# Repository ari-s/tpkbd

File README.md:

TPKBD - a USB interface for thinkpad keyboards
=

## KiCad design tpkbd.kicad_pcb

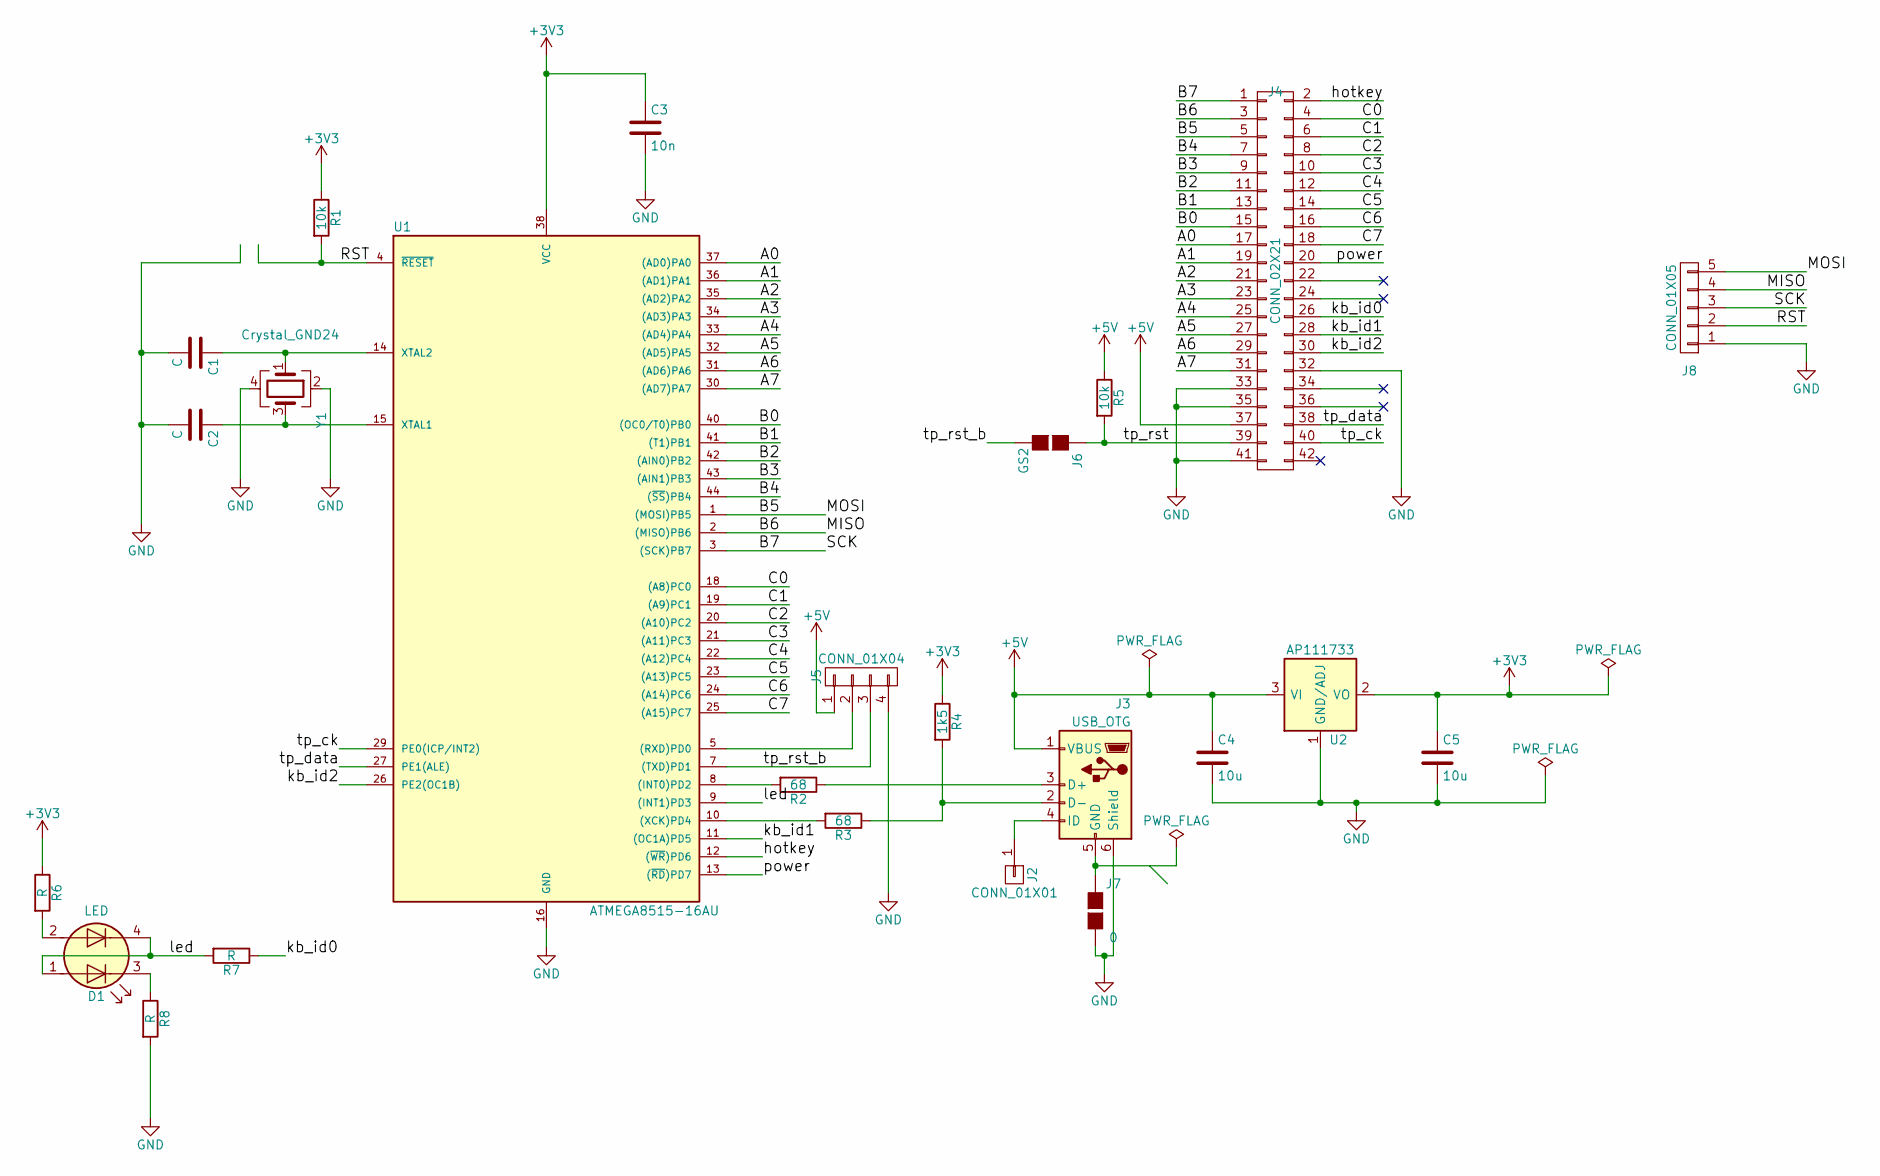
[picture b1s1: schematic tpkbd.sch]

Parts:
C1, C2: C; C_0603_HandSoldering
C3: 10n; C_0603_HandSoldering
C4, C5: 10u; C_0805_HandSoldering
D1: LED; PLCC4
J2: CONN_01X01; Pins1x1
J3: USB_OTG; USB_Micro-B
J4: CONN_02X21; KX14
J5: CONN_01X04; Pin_Header_Straight_1x04
J6: GS2; C_0402
J7: 0; C_0402
J8: CONN_01X05; Pins_1x5
R1, R5: 10k; R_0603_HandSoldering
R2, R3: 68; R_0603_HandSoldering
R4: 1k5; R_0603_HandSoldering
R6, R7, R8: R; R_0603_HandSoldering
U1: ATMEGA8515-16AU; LQFP-44_10x10mm_Pitch0.8mm
U2: AP111733; SOT-223
Y1: Crystal_GND24; Crystal_SMD_0603_4Pads

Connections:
+3V3: C3.1, C5.1, R1.1, R4.1, R6.1, U1.38 (VCC), U2.2 (VO), U2.4 (VO)
+5V: C4.1, J3.1 (VBUS), J4.37, J5.1, R5.1, U2.3 (VI)
/A0: J4.17, U1.37 ((AD0)PA0)
/A1: J4.19, U1.36 ((AD1)PA1)
/A2: J4.21, U1.35 ((AD2)PA2)
/A3: J4.23, U1.34 ((AD3)PA3)
/A4: J4.25, U1.33 ((AD4)PA4)
/A5: J4.27, U1.32 ((AD5)PA5)
/A6: J4.29, U1.31 ((AD6)PA6)
/A7: J4.31, U1.30 ((AD7)PA7)
/B0: J4.15, U1.40 ((OC0/T0)PB0)
/B1: J4.13, U1.41 ((T1)PB1)
/B2: J4.11, U1.42 ((AIN0)PB2)
/B3: J4.9, U1.43 ((AIN1)PB3)
/B4: J4.7, U1.44 ((~SS~)PB4)
/B5: J4.5, J8.5, U1.1 ((MOSI)PB5)
/B6: J4.3, J8.4, U1.2 ((MISO)PB6)
/B7: J4.1, J8.3, U1.3 ((SCK)PB7)
/C0: J4.4, U1.18 ((A8)PC0)
/C1: J4.6, U1.19 ((A9)PC1)
/C2: J4.8, U1.20 ((A10)PC2)
/C3: J4.10, U1.21 ((A11)PC3)
/C4: J4.12, U1.22 ((A12)PC4)
/C5: J4.14, U1.23 ((A13)PC5)
/C6: J4.16, U1.24 ((A14)PC6)
/C7: J4.18, U1.25 ((A15)PC7)
/RST: J8.2, R1.2, U1.4 (~RESET)
/hotkey: J4.2, U1.12 ((~WR~)PD6)
/kb_id0: J4.26, R7.1
/kb_id1: J4.28, U1.11 ((OC1A)PD5)
/kb_id2: J4.30, U1.26 (PE2(OC1B))
/led: D1.1 (A1), D1.4 (K2), R7.2, U1.9 ((INT1)PD3)
/power: J4.20, U1.13 ((~RD~)PD7)
/tp_ck: J4.40, U1.29 (PE0(ICP/INT2))
/tp_data: J4.38, U1.27 (PE1(ALE))
/tp_rst: J4.39, J6.1 (G1), R5.2
/tp_rst_b: J5.3, J6.2 (G2), U1.7 ((TXD)PD1)
GND: C1.2, C2.2, C3.2, C4.2, C5.2, J3.6 (Shield), J4.32, J4.33, J4.35, J4.41, J4.42, J4.43, J4.44, J5.4, J7.2 (G2), J8.1, R8.2, U1.6, U1.16 (GND), U2.1 (GND/ADJ), Y1.2, Y1.4
unnamed: C1.1, U1.14 (XTAL2), Y1.1
unnamed: C2.1, U1.15 (XTAL1), Y1.3
unnamed: D1.2 (A2), R6.2
unnamed: D1.3 (K1), R8.1
unnamed: J2.1, J3.4 (ID)
unnamed: J3.2 (D-), R3.1, R4.2
unnamed: J3.3 (D+), R2.1
unnamed: J3.5 (GND), J7.1 (G1)
unnamed: J5.2, U1.5 ((RXD)PD0)
unnamed: R2.2, U1.8 ((INT0)PD2)
unnamed: R3.2, U1.10 ((XCK)PD4)

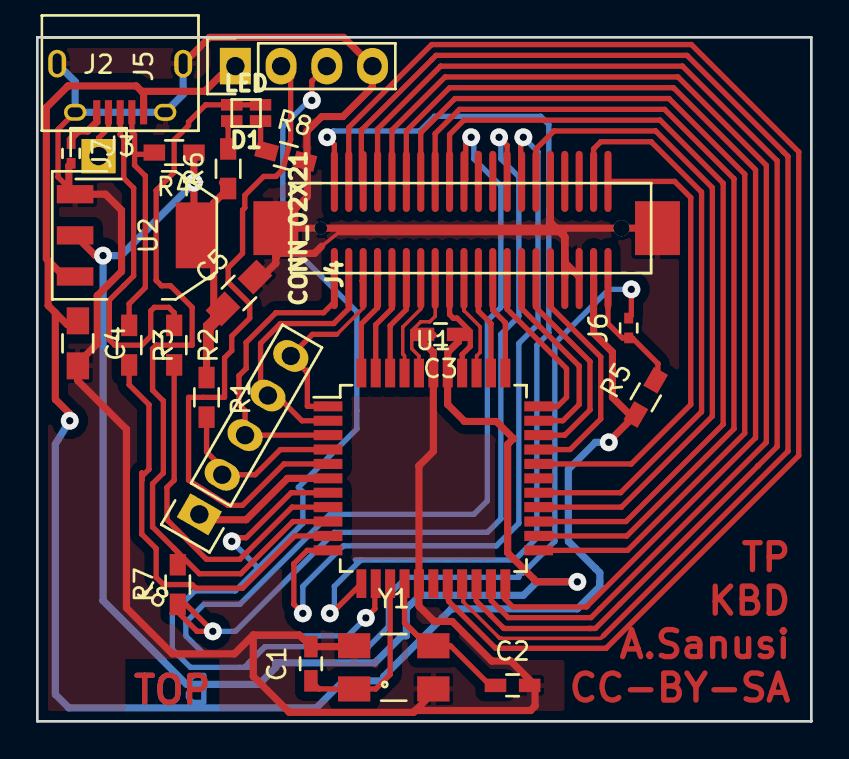
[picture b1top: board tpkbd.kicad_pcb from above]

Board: 2 copper layers, 43.0 x 38.0 mm, 24 parts (0 on the bottom side), 49 nets.

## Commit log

2017-09-14 fixed tx14 conn
2017-09-14 seems complete :)
2017-09-15 initial readme
2017-09-15 added a LED
2017-09-15 cleanup
2017-09-15 cleanup2
2018-06-09 schema: add values of components
2018-06-09 add mounting holes

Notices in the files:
tpkbd.kicad_pcb:
CC-BY-SA
